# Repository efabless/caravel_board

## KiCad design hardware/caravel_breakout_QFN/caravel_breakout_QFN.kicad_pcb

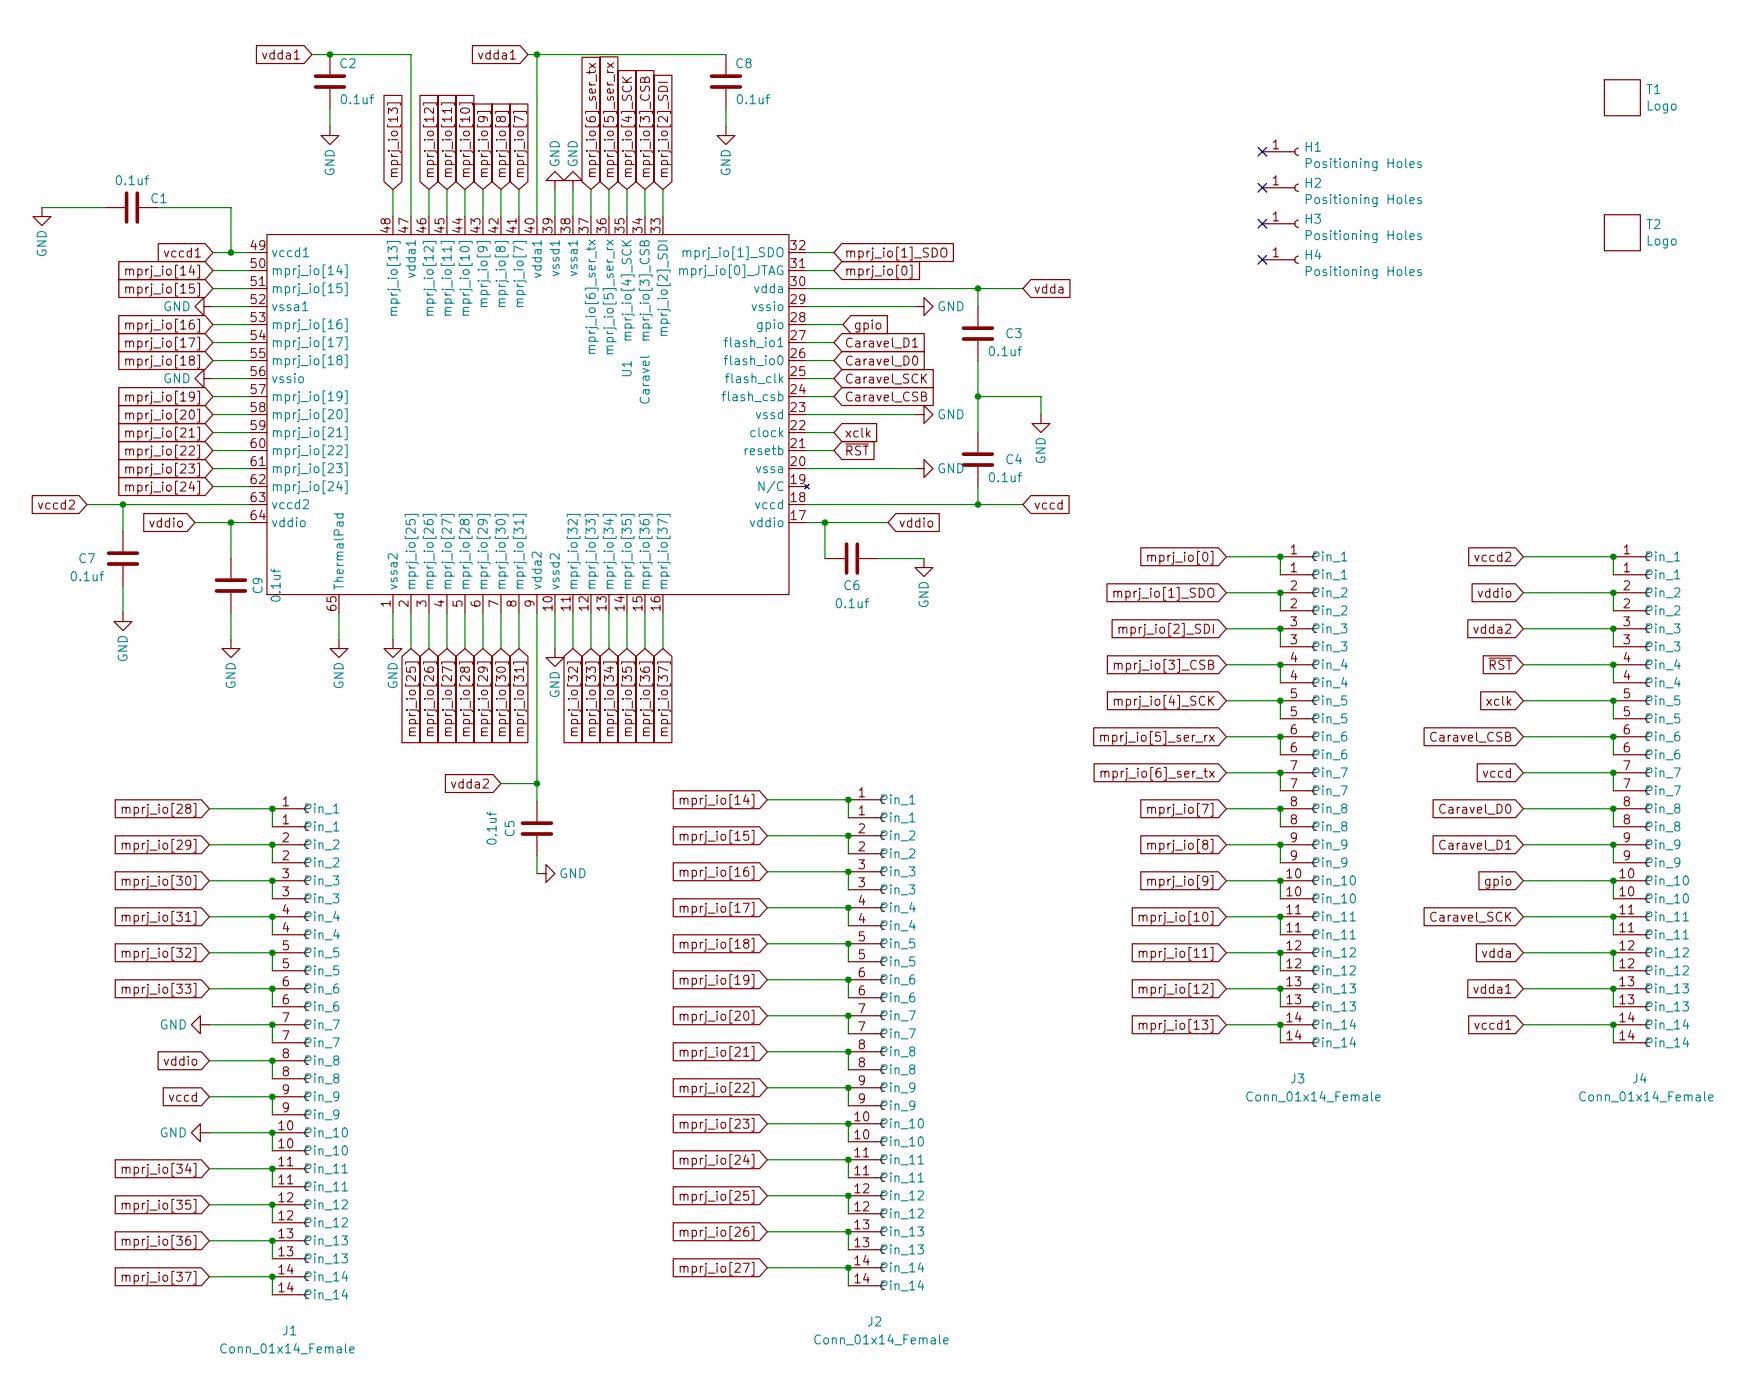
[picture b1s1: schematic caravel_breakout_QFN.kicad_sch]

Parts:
C1, C2, C3, C4, C5, C6, C7, C8, C9: 0.1uf; C_0402_1005Metric
H1, H2, H3, H4: Positioning Holes; MountingHole_2.2mm_M2_ISO7380_Pad
J1, J2, J3, J4: Conn_01x14_Female; Caravel_Breakout_Connectors_2x14
T1: Logo; logo_small
T2: Logo; ef_logo
U1: Caravel; QFN-64-1EP_9x9mm_P0.5mm_EP7.65x7.65mm

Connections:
Caravel_CSB: J4.6, U1.24 (flash_csb)
Caravel_D0: J4.8, U1.26 (flash_io0)
Caravel_D1: J4.9, U1.27 (flash_io1)
Caravel_SCK: J4.11, U1.25 (flash_clk)
GND: C1.1, C2.2, C3.2, C4.1, C5.1, C6.1, C7.1, C8.2, C9.1, J1.7, J1.10, U1.1 (vssa2), U1.10 (vssd2), U1.20 (vssa), U1.23 (vssd), U1.29 (vssio), U1.38 (vssa1), U1.39 (vssd1), U1.52 (vssa1), U1.56 (vssio), U1.65 (ThermalPad)
gpio: J4.10, U1.28 (gpio)
mprj_io[0]: J3.1, U1.31 (mprj_io[0]_JTAG)
mprj_io[1]_SDO: J3.2, U1.32 (mprj_io[1]_SDO)
mprj_io[2]_SDI: J3.3, U1.33 (mprj_io[2]_SDI)
mprj_io[3]_CSB: J3.4, U1.34 (mprj_io[3]_CSB)
mprj_io[4]_SCK: J3.5, U1.35 (mprj_io[4]_SCK)
mprj_io[5]_ser_rx: J3.6, U1.36 (mprj_io[5]_ser_rx)
mprj_io[6]_ser_tx: J3.7, U1.37 (mprj_io[6]_ser_tx)
mprj_io[7]: J3.8, U1.41 (mprj_io[7])
mprj_io[8]: J3.9, U1.42 (mprj_io[8])
mprj_io[9]: J3.10, U1.43 (mprj_io[9])
mprj_io[10]: J3.11, U1.44 (mprj_io[10])
mprj_io[11]: J3.12, U1.45 (mprj_io[11])
mprj_io[12]: J3.13, U1.46 (mprj_io[12])
mprj_io[13]: J3.14, U1.48 (mprj_io[13])
mprj_io[14]: J2.1, U1.50 (mprj_io[14])
mprj_io[15]: J2.2, U1.51 (mprj_io[15])
mprj_io[16]: J2.3, U1.53 (mprj_io[16])
mprj_io[17]: J2.4, U1.54 (mprj_io[17])
mprj_io[18]: J2.5, U1.55 (mprj_io[18])
mprj_io[19]: J2.6, U1.57 (mprj_io[19])
mprj_io[20]: J2.7, U1.58 (mprj_io[20])
mprj_io[21]: J2.8, U1.59 (mprj_io[21])
mprj_io[22]: J2.9, U1.60 (mprj_io[22])
mprj_io[23]: J2.10, U1.61 (mprj_io[23])
mprj_io[24]: J2.11, U1.62 (mprj_io[24])
mprj_io[25]: J2.12, U1.2 (mprj_io[25])
mprj_io[26]: J2.13, U1.3 (mprj_io[26])
mprj_io[27]: J2.14, U1.4 (mprj_io[27])
mprj_io[28]: J1.1, U1.5 (mprj_io[28])
mprj_io[29]: J1.2, U1.6 (mprj_io[29])
mprj_io[30]: J1.3, U1.7 (mprj_io[30])
mprj_io[31]: J1.4, U1.8 (mprj_io[31])
mprj_io[32]: J1.5, U1.11 (mprj_io[32])
mprj_io[33]: J1.6, U1.12 (mprj_io[33])
mprj_io[34]: J1.11, U1.13 (mprj_io[34])
mprj_io[35]: J1.12, U1.14 (mprj_io[35])
mprj_io[36]: J1.13, U1.15 (mprj_io[36])
mprj_io[37]: J1.14, U1.16 (mprj_io[37])
vccd: C4.2, J1.9, J4.7, U1.18 (vccd)
vccd1: C1.2, J4.14, U1.49 (vccd1)
vccd2: C7.2, J4.1, U1.63 (vccd2)
vdda: C3.1, J4.12, U1.30 (vdda)
vdda1: C2.1, C8.1, J4.13, U1.40 (vdda1), U1.47 (vdda1)
vdda2: C5.2, J4.3, U1.9 (vdda2)
vddio: C6.2, C9.2, J1.8, J4.2, U1.17 (vddio), U1.64 (vddio)
xclk: J4.5, U1.22 (clock)
~RST: J4.4, U1.21 (resetb)

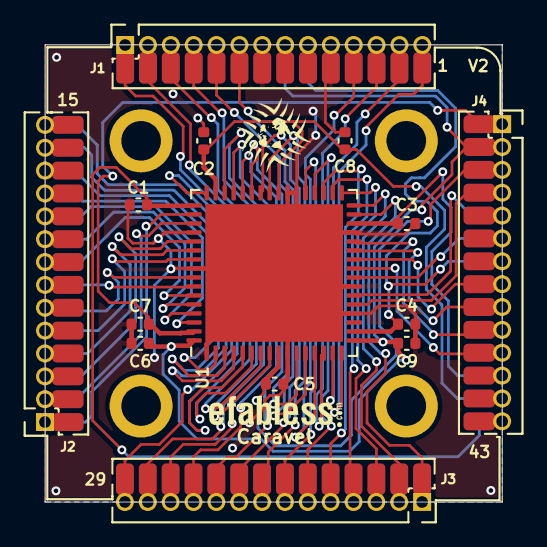
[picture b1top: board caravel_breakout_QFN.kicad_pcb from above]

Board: 2 copper layers, 25.4 x 25.4 mm, 20 parts (0 on the bottom side), 53 nets.

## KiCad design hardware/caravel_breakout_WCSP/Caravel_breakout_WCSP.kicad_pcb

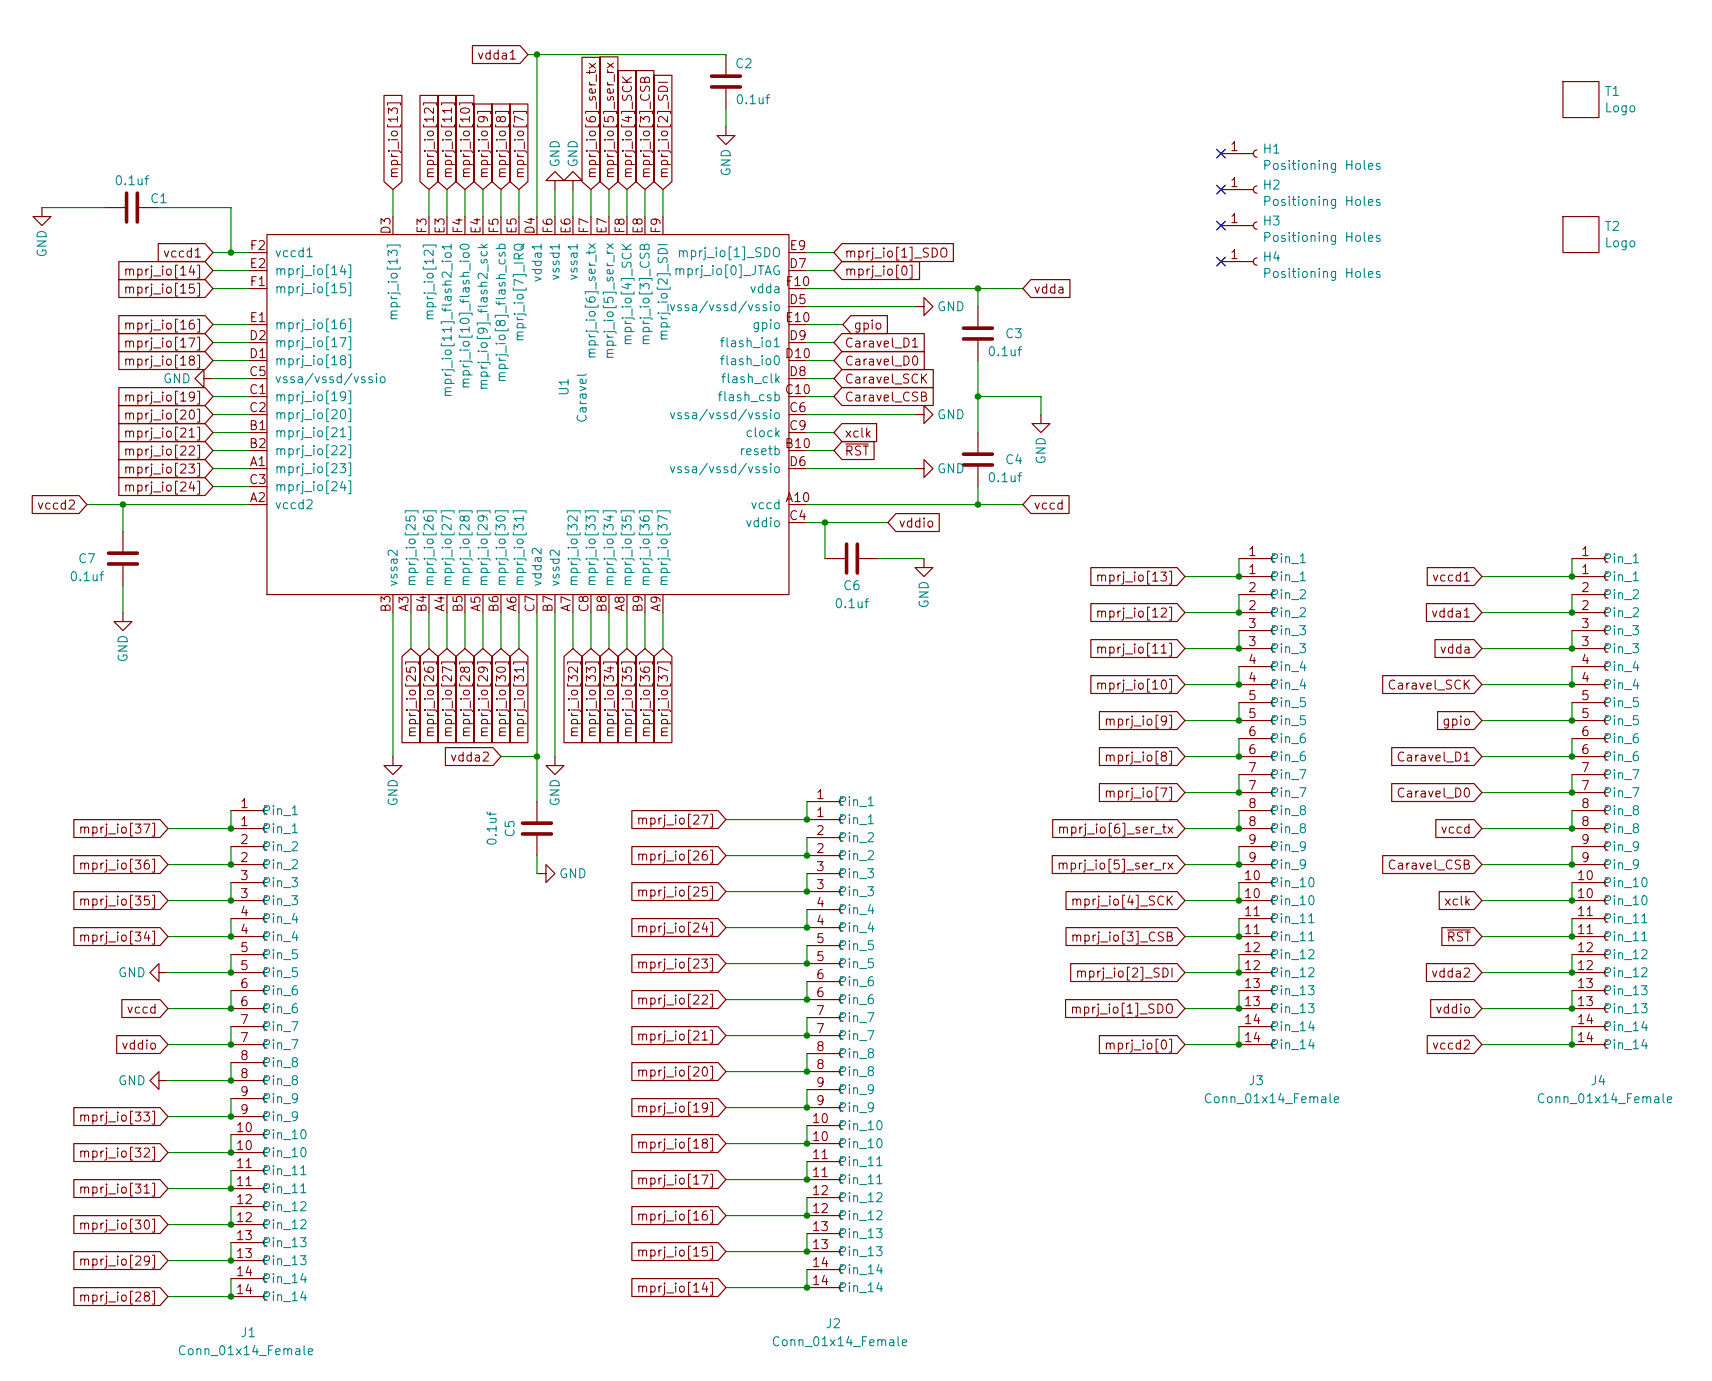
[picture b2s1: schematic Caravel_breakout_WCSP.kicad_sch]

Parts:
C1, C2, C3, C4, C5, C6, C7: 0.1uf; C_0603_1608Metric
H1, H2, H3, H4: Positioning Holes; MountingHole_2.2mm_M2_ISO7380_Pad
J1, J2, J3, J4: Conn_01x14_Female; Caravel_Breakout_Connectors_2x14
T1: Logo; logo
T2: Logo; ef_logo
U1: Caravel; Caravel_WCSP

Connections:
Caravel_CSB: J4.9, U1.C10 (flash_csb)
Caravel_D0: J4.7, U1.D10 (flash_io0)
Caravel_D1: J4.6, U1.D9 (flash_io1)
Caravel_SCK: J4.4, U1.D8 (flash_clk)
GND: C1.1, C2.2, C3.2, C4.1, C5.1, C6.1, C7.1, J1.5, J1.8, U1.B3 (vssa2), U1.B7 (vssd2), U1.C5 (vssa/vssd/vssio), U1.C6 (vssa/vssd/vssio), U1.D5 (vssa/vssd/vssio), U1.D6 (vssa/vssd/vssio), U1.E6 (vssa1), U1.F6 (vssd1)
gpio: J4.5, U1.E10 (gpio)
mprj_io[0]: J3.14, U1.D7 (mprj_io[0]_JTAG)
mprj_io[1]_SDO: J3.13, U1.E9 (mprj_io[1]_SDO)
mprj_io[2]_SDI: J3.12, U1.F9 (mprj_io[2]_SDI)
mprj_io[3]_CSB: J3.11, U1.E8 (mprj_io[3]_CSB)
mprj_io[4]_SCK: J3.10, U1.F8 (mprj_io[4]_SCK)
mprj_io[5]_ser_rx: J3.9, U1.E7 (mprj_io[5]_ser_rx)
mprj_io[6]_ser_tx: J3.8, U1.F7 (mprj_io[6]_ser_tx)
mprj_io[7]: J3.7, U1.E5 (mprj_io[7]_IRQ)
mprj_io[8]: J3.6, U1.F5 (mprj_io[8]_flash_csb)
mprj_io[9]: J3.5, U1.E4 (mprj_io[9]_flash2_sck)
mprj_io[10]: J3.4, U1.F4 (mprj_io[10]_flash_io0)
mprj_io[11]: J3.3, U1.E3 (mprj_io[11]_flash2_io1)
mprj_io[12]: J3.2, U1.F3 (mprj_io[12])
mprj_io[13]: J3.1, U1.D3 (mprj_io[13])
mprj_io[14]: J2.14, U1.E2 (mprj_io[14])
mprj_io[15]: J2.13, U1.F1 (mprj_io[15])
mprj_io[16]: J2.12, U1.E1 (mprj_io[16])
mprj_io[17]: J2.11, U1.D2 (mprj_io[17])
mprj_io[18]: J2.10, U1.D1 (mprj_io[18])
mprj_io[19]: J2.9, U1.C1 (mprj_io[19])
mprj_io[20]: J2.8, U1.C2 (mprj_io[20])
mprj_io[21]: J2.7, U1.B1 (mprj_io[21])
mprj_io[22]: J2.6, U1.B2 (mprj_io[22])
mprj_io[23]: J2.5, U1.A1 (mprj_io[23])
mprj_io[24]: J2.4, U1.C3 (mprj_io[24])
mprj_io[25]: J2.3, U1.A3 (mprj_io[25])
mprj_io[26]: J2.2, U1.B4 (mprj_io[26])
mprj_io[27]: J2.1, U1.A4 (mprj_io[27])
mprj_io[28]: J1.14, U1.B5 (mprj_io[28])
mprj_io[29]: J1.13, U1.A5 (mprj_io[29])
mprj_io[30]: J1.12, U1.B6 (mprj_io[30])
mprj_io[31]: J1.11, U1.A6 (mprj_io[31])
mprj_io[32]: J1.10, U1.A7 (mprj_io[32])
mprj_io[33]: J1.9, U1.C8 (mprj_io[33])
mprj_io[34]: J1.4, U1.B8 (mprj_io[34])
mprj_io[35]: J1.3, U1.A8 (mprj_io[35])
mprj_io[36]: J1.2, U1.B9 (mprj_io[36])
mprj_io[37]: J1.1, U1.A9 (mprj_io[37])
vccd: C4.2, J1.6, J4.8, U1.A10 (vccd)
vccd1: C1.2, J4.1, U1.F2 (vccd1)
vccd2: C7.2, J4.14, U1.A2 (vccd2)
vdda: C3.1, J4.3, U1.F10 (vdda)
vdda1: C2.1, J4.2, U1.D4 (vdda1)
vdda2: C5.2, J4.12, U1.C7 (vdda2)
vddio: C6.2, J1.7, J4.13, U1.C4 (vddio)
xclk: J4.10, U1.C9 (clock)
~RST: J4.11, U1.B10 (resetb)

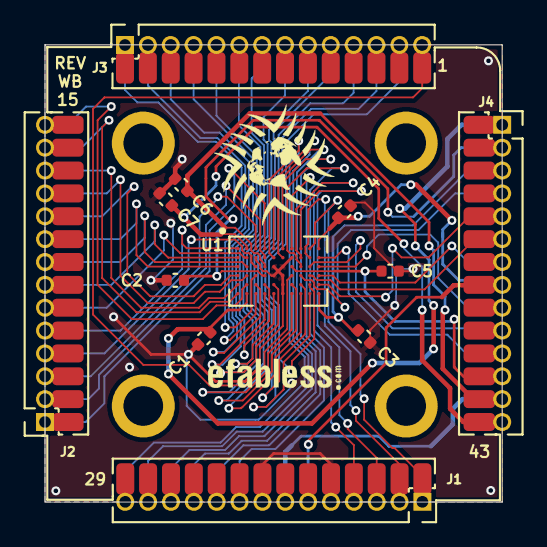
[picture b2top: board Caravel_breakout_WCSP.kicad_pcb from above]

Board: 2 copper layers, 25.4 x 25.4 mm, 18 parts (0 on the bottom side), 53 nets.

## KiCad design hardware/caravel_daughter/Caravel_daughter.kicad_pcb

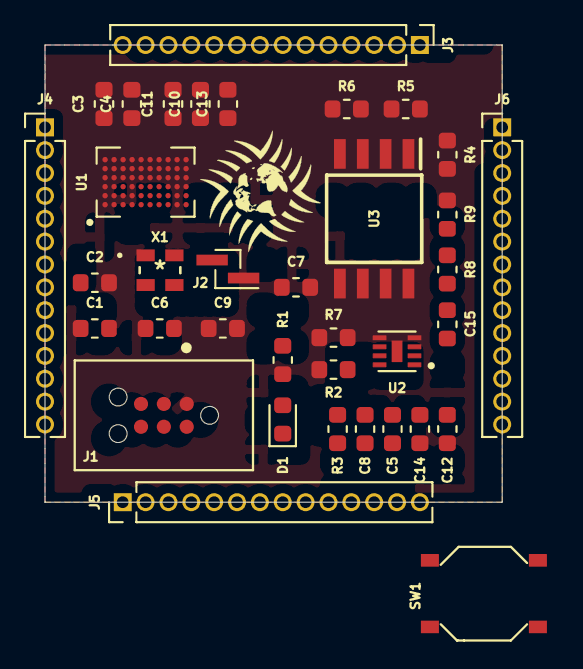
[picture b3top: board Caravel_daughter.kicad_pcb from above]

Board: 2 copper layers, 25.4 x 25.4 mm, 37 parts (0 on the bottom side), 57 nets, no tracks yet.

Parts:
C1, C2, C3, C4, C6, C7, C8, C9, C10, C11, C13, C15: 0.1uf; C_0603_1608Metric
C5: 10uf; C_0603_1608Metric
C12, C14: 2.2uf; C_0603_1608Metric
D1: LED - 17-215SURC/S530-A2/TR8; LED_0603_1608Metric
J1: TC2030-IDC-NL; TAG_TC2030-IDC-NL
J2: Conn_01x02_Male; PinHeader_1x02_P1.00mm_Vertical_SMD_Pin1Left
J3, J4, J5, J6: Conn_01x14_Female; PinHeader_1x14_P1.27mm_Vertical
R1: 82 - 0805W8F820JT5E; R_0603_1608Metric
R2, R3: 100; R_0603_1608Metric
R4, R5, R6, R7, R8, R9: 10k; R_0603_1608Metric
SW1: SW_Push - SKQGADE010; SW4-SMD-5.2X5.2X1.5MM
T1: Logo; logo
U1: Caravel; Caravel_WCSP
U2: MIC5350-SGYMT-TR; SON50P200X200X60-9N
U3: W25Q32FVSS; SOIC127P790X216-8N
X1: DSC6001_10MHZ; DSC6001JE1A-010.0000

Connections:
+1V8: C11.2, C14.2, J6.2, J6.3, U1.A10, U2.7
+3V3: C12.2, C13.1, J6.6, J6.7, R1.1, U1.F10, U2.8
+5V: C5.2, J1.6, J6.14, R2.2, R3.2, U2.1
Caravel_CSB: R4.1, U1.C10, U3.1
Caravel_D0: R7.1, U1.D10, U3.5
Caravel_D1: R5.1, U1.D9, U3.2
Caravel_SCK: R8.1, U1.D8, U3.6
GND: C1.1, C2.1, C3.2, C4.1, C5.1, C6.1, C7.2, C8.1, C9.1, C10.1, C11.1, C12.1, C13.2, C14.1, C15.2, J1.1, J2.2, SW1.2, U1.B3, U1.B7, U1.C5, U1.C6, U1.D5, U1.D6, U1.E6, U1.F6, U2.2, U2.9, U3.4, X1.2
unnamed: C8.2, U2.3
unnamed: D1.2, R1.2
unnamed: J2.1, X1.1
unnamed: R2.1, U2.4
unnamed: R3.1, U2.5
unnamed: R6.1, U3.3
unnamed: R9.1, U3.7
gpio: D1.1, U1.E10
mprj_io[0]: J3.1, U1.D7
mprj_io[1]_SDO: J3.2, U1.E9
mprj_io[2]_SDI: J3.3, U1.F9
mprj_io[3]_CSB: J3.4, U1.E8
mprj_io[4]_SCK: J3.5, U1.F8
mprj_io[5]_ser_rx: J1.2, J3.6, U1.E7
mprj_io[6]_ser_tx: J1.3, J3.7, U1.F7
mprj_io[7]: J3.8, U1.E5
mprj_io[8]: J3.9, U1.F5
mprj_io[9]: J3.10, U1.E4
mprj_io[10]: J3.11, U1.F4
mprj_io[11]: J3.12, U1.E3
mprj_io[12]: J3.13, U1.F3
mprj_io[13]: J3.14, U1.D3
mprj_io[14]: J4.1, U1.E2
mprj_io[15]: J4.2, U1.F1
mprj_io[16]: J4.3, U1.E1
mprj_io[17]: J4.4, U1.D2
mprj_io[18]: J4.5, U1.D1
mprj_io[19]: J4.6, U1.C1
mprj_io[20]: J4.7, U1.C2
mprj_io[21]: J4.8, U1.B1
mprj_io[22]: J4.9, U1.B2
mprj_io[23]: J4.10, U1.A1
mprj_io[24]: J4.11, U1.C3
mprj_io[25]: J4.12, U1.A3
mprj_io[26]: J4.13, U1.B4
mprj_io[27]: J4.14, U1.A4
mprj_io[28]: J5.1, U1.B5
mprj_io[29]: J5.2, U1.A5
mprj_io[30]: J5.3, U1.B6
mprj_io[31]: J5.4, U1.A6
mprj_io[32]: J5.5, U1.A7
mprj_io[33]: J5.6, U1.C8
vccd1: C3.1, J6.4, U1.F2
vccd2: C1.2, J6.1, U1.A2
vdda1: C4.2, C7.1, J6.8, U1.D4
vdda2: C6.2, J6.5, U1.C7
vddio: C2.2, C9.2, C10.2, C15.1, R4.2, R5.2, R6.2, R7.2, R8.2, R9.2, U1.C4, U3.8, X1.4
xclk: U1.C9, X1.3
~RST: SW1.1, U1.B10

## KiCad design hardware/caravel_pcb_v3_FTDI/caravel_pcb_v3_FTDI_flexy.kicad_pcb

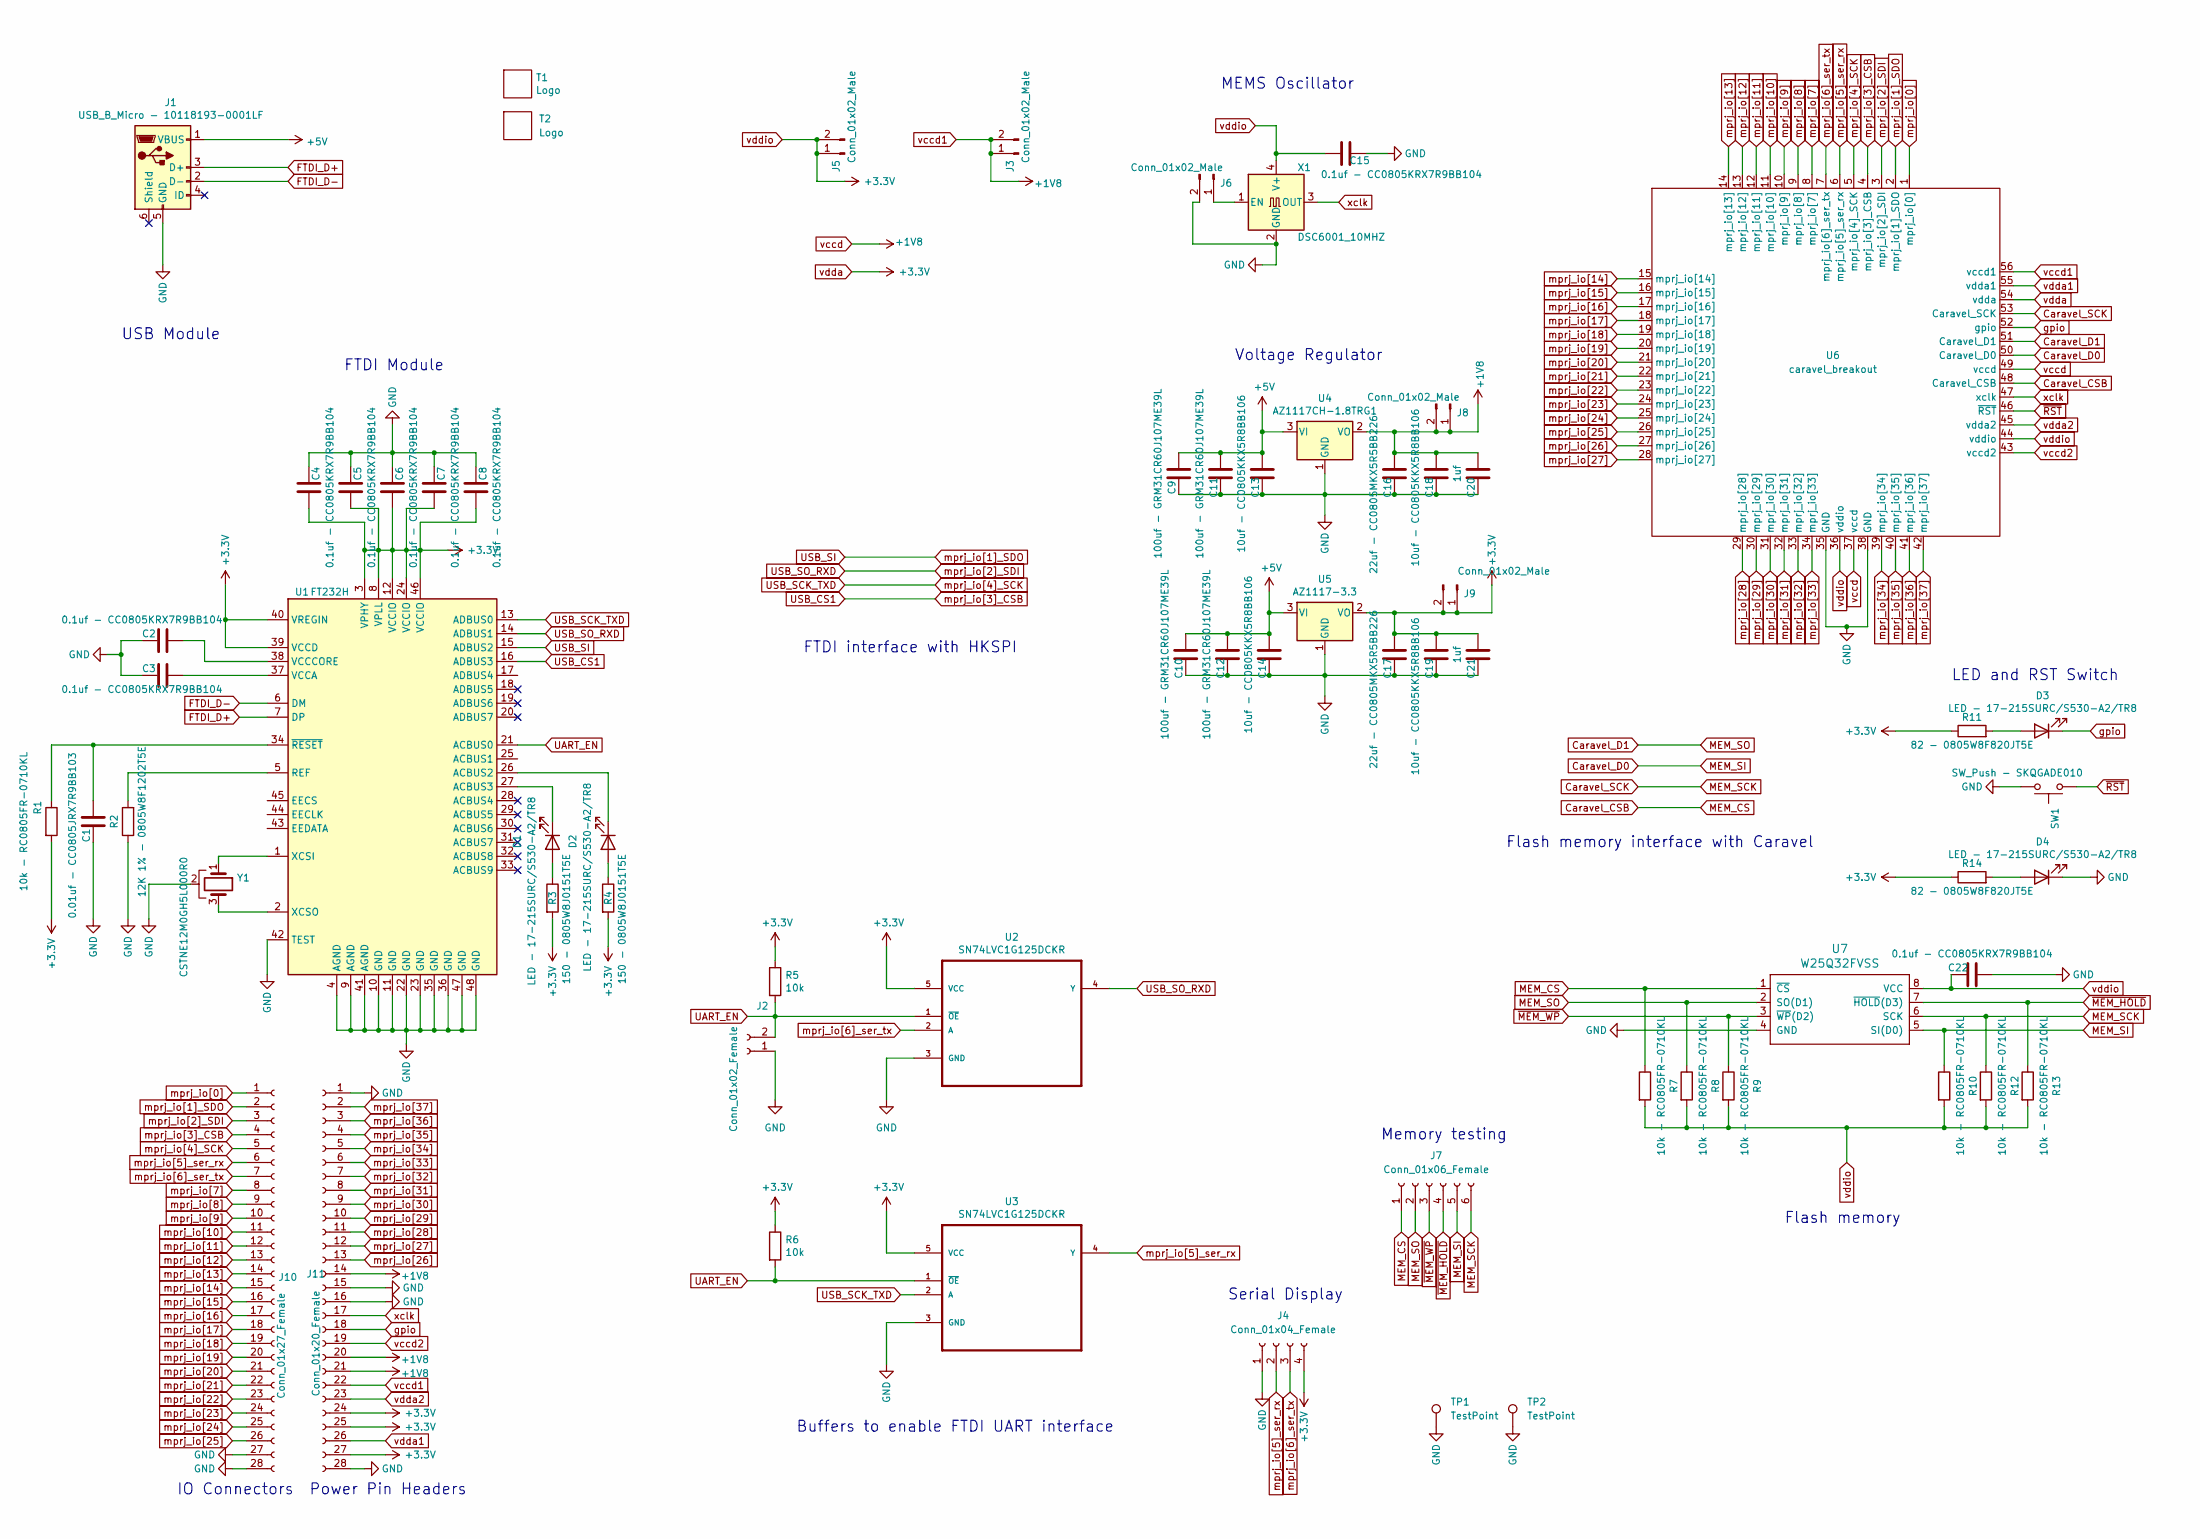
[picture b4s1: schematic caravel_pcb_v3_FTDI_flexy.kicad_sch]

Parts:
C1: 0.01uf - CC0805JRX7R9BB103; C_0805_2012Metric
C2, C3, C4, C5, C6, C7, C8, C15, C22: 0.1uf - CC0805KRX7R9BB104; C_0805_2012Metric
C9, C10, C11, C12: 100uf - GRM31CR60J107ME39L; C_1206_3216Metric
C13, C14, C18, C19: 10uf - CC0805KKX5R8BB106; C_0805_2012Metric
C16, C17: 22uf - CC0805MKX5R5BB226; C_0805_2012Metric
C20, C21: 1uf; C_0805_2012Metric
D1, D2, D3, D4: LED - 17-215SURC/S530-A2/TR8; LED_1206_3216Metric
J1: USB_B_Micro - 10118193-0001LF; FCI_10118193-0001LF
J2: Conn_01x02_Female; PinHeader_1x02_P2.54mm_Vertical
J3, J5, J6, J8, J9: Conn_01x02_Male; PinHeader_1x02_P2.54mm_Vertical
J4: Conn_01x04_Female; PinHeader_1x04_P2.54mm_Vertical
J7: Conn_01x06_Female; PinHeader_1x06_P2.54mm_Vertical
J10: Conn_01x27_Female; PinHeader_1x27_P2.54mm_Vertical
J11: Conn_01x20_Female; PinHeader_1x20_P2.54mm_Vertical
R1, R7, R8, R9, R10, R12, R13: 10k - RC0805FR-0710KL; R_0805_2012Metric
R2: 12K 1% - 0805W8F1202T5E; R_0805_2012Metric
R3, R4: 150 - 0805W8J0151T5E; R_0805_2012Metric
R5, R6: 10k; R_0805_2012Metric
R11, R14: 82 - 0805W8F820JT5E; R_0805_2012Metric
SW1: SW_Push - SKQGADE010; SW4-SMD-5.2X5.2X1.5MM
T1: Logo; logo
T2: Logo; ef_logo
TP1, TP2: TestPoint; TestPoint_Bridge_Pitch2.54mm_Drill1.0mm
U1: FT232H; QFN-48-1EP_8x8mm_P0.5mm_EP6.2x6.2mm
U2, U3: SN74LVC1G125DCKR; SOT65P210X110-5N
U4: AZ1117CH-1.8TRG1; SOT-223
U5: AZ1117-3.3; SOT-223
U6: caravel_breakout; caravel_breakout_flexy
U7: W25Q32FVSS; SOIC127P790X216-8N
X1: DSC6001_10MHZ; DSC6001JE1A-010.0000
Y1: CSTNE12M0GH5L000R0

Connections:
+5V: C9.2, C10.2, C11.2, C12.2, C13.2, C14.2, J1.1 (VBUS), U4.3 (VI), U5.3 (VI)
Caravel_CSB: J7.1, R7.1, U6.48 (Caravel_CSB), U7.1 (~CS)
Caravel_D0: J7.5, R10.1, U6.50 (Caravel_D0), U7.5 (SI(D0))
Caravel_D1: J7.2, R8.1, U6.51 (Caravel_D1), U7.2 (SO(D1))
Caravel_SCK: J7.6, R12.1, U6.53 (Caravel_SCK), U7.6 (SCK)
FTDI_D+: J1.3 (D+), U1.7 (DP)
FTDI_D-: J1.2 (D-), U1.6 (DM)
GND: C1.1, C2.1, C3.1, C4.1, C5.1, C6.1, C7.1, C8.1, C9.1, C10.1, C11.1, C12.1, C13.1, C14.1, C15.1, C16.1, C17.1, C18.1, C19.1, C20.1, C21.1, C22.2, D4.1 (K), J1.5 (GND), J2.1, J4.1, J6.2, J10.27, J10.28, J11.1, J11.15, J11.16, J11.28, R2.1, SW1.2, TP1.1, TP2.1, U1.4 (AGND), U1.9 (AGND), U1.10 (GND), U1.11 (GND), U1.22 (GND), U1.23 (GND), U1.35 (GND), U1.36 (GND), U1.41 (AGND), U1.42 (TEST), U1.47 (GND), U1.48 (GND), U2.3 (GND), U3.3 (GND), U4.1 (GND), U5.1 (GND), U6.35 (GND), U6.38 (GND), U7.4 (GND), X1.2 (GND), Y1.2
unnamed: C1.2, R1.1, U1.34 (~RESET)
unnamed: C2.2, U1.38 (VCCCORE)
unnamed: C3.2, U1.37 (VCCA)
unnamed: D1.1 (K), U1.27 (ACBUS3)
unnamed: D1.2 (A), R3.1
unnamed: D2.1 (K), U1.26 (ACBUS2)
unnamed: D2.2 (A), R4.1
unnamed: D3.2 (A), R11.2
unnamed: D4.2 (A), R14.2
unnamed: J6.1, X1.1 (EN)
unnamed: R2.2, U1.5 (REF)
unnamed: U1.1 (XCSI), Y1.1
unnamed: U1.2 (XCSO), Y1.3
UART_EN: J2.2, R5.2, R6.2, U1.21 (ACBUS0), U2.1 (~OE), U3.1 (~OE)
USB_CS1: J10.4, U1.16 (ADBUS3), U6.4 (mprj_io[3]_CSB)
USB_SCK_TXD: J10.5, U1.13 (ADBUS0), U3.2 (A), U6.5 (mprj_io[4]_SCK)
USB_SI: J10.2, U1.15 (ADBUS2), U6.2 (mprj_io[1]_SDO)
USB_SO_RXD: J10.3, U1.14 (ADBUS1), U2.4 (Y), U6.3 (mprj_io[2]_SDI)
gpio: D3.1 (K), J11.18, U6.52 (gpio)
mprj_io[0]: J10.1, U6.1 (mprj_io[0])
mprj_io[5]_ser_rx: J4.2, J10.6, U3.4 (Y), U6.6 (mprj_io[5]_ser_rx)
mprj_io[6]_ser_tx: J4.3, J10.7, U2.2 (A), U6.7 (mprj_io[6]_ser_tx)
mprj_io[7]: J10.8, U6.8 (mprj_io[7])
mprj_io[8]: J10.9, U6.9 (mprj_io[8])
mprj_io[9]: J10.10, U6.10 (mprj_io[9])
mprj_io[10]: J10.11, U6.11 (mprj_io[10])
mprj_io[11]: J10.12, U6.12 (mprj_io[11])
mprj_io[12]: J10.13, U6.13 (mprj_io[12])
mprj_io[13]: J10.14, U6.14 (mprj_io[13])
mprj_io[14]: J10.15, U6.15 (mprj_io[14])
mprj_io[15]: J10.16, U6.16 (mprj_io[15])
mprj_io[16]: J10.17, U6.17 (mprj_io[16])
mprj_io[17]: J10.18, U6.18 (mprj_io[17])
mprj_io[18]: J10.19, U6.19 (mprj_io[18])
mprj_io[19]: J10.20, U6.20 (mprj_io[19])
mprj_io[20]: J10.21, U6.21 (mprj_io[20])
mprj_io[21]: J10.22, U6.22 (mprj_io[21])
mprj_io[22]: J10.23, U6.23 (mprj_io[22])
mprj_io[23]: J10.24, U6.24 (mprj_io[23])
mprj_io[24]: J10.25, U6.25 (mprj_io[24])
mprj_io[25]: J10.26, U6.26 (mprj_io[25])
mprj_io[26]: J11.13, U6.27 (mprj_io[26])
mprj_io[27]: J11.12, U6.28 (mprj_io[27])
mprj_io[28]: J11.11, U6.29 (mprj_io[28])
mprj_io[29]: J11.10, U6.30 (mprj_io[29])
mprj_io[30]: J11.9, U6.31 (mprj_io[30])
mprj_io[31]: J11.8, U6.32 (mprj_io[31])
mprj_io[32]: J11.7, U6.33 (mprj_io[32])
mprj_io[33]: J11.6, U6.34 (mprj_io[33])
mprj_io[34]: J11.5, U6.39 (mprj_io[34])
mprj_io[35]: J11.4, U6.40 (mprj_io[35])
mprj_io[36]: J11.3, U6.41 (mprj_io[36])
mprj_io[37]: J11.2, U6.42 (mprj_io[37])
vccd1: C16.2, C18.2, C20.2, J3.1, J3.2, J8.1, J8.2, J11.14, J11.20, J11.21, J11.22, U4.2 (VO), U6.37 (vccd), U6.49 (vccd), U6.56 (vccd1)
vccd2: J11.19, U6.43 (vccd2)
vdda: C4.2, C5.2, C6.2, C7.2, C8.2, C15.2, C17.2, C19.2, C21.2, C22.1, J4.4, J5.1, J5.2, J9.1, J9.2, J11.24, J11.25, J11.27, R1.2, R3.2, R4.2, R5.1, R6.1, R7.2, R8.2, R9.2, R10.2, R11.1, R12.2, R13.2, R14.1, U1.3 (VPHY), U1.8 (VPLL), U1.12 (VCCIO), U1.24 (VCCIO), U1.39 (VCCD), U1.40 (VREGIN), U1.46 (VCCIO), U2.5 (VCC), U3.5 (VCC), U5.2 (VO), U6.36 (vddio), U6.44 (vddio), U6.54 (vdda), U7.8 (VCC), X1.4 (V+)
vdda1: J11.26, U6.55 (vdda1)
vdda2: J11.23, U6.45 (vdda2)
xclk: J11.17, U6.47 (xclk), X1.3 (OUT)
~MEM_HOLD: J7.4, R13.1, U7.7 (~HOLD(D3))
~MEM_WP: J7.3, R9.1, U7.3 (~WP(D2))
~RST: SW1.1, U6.46 (~RST)

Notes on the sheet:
Serial Display
LED and RST Switch
Flash memory interface with Caravel
Flash memory
Memory testing
FTDI interface with HKSPI
Power Pin Headers
Voltage Regulator
IO Connectors
FTDI Module
USB Module
MEMS Oscillator
Buffers to enable FTDI UART interface

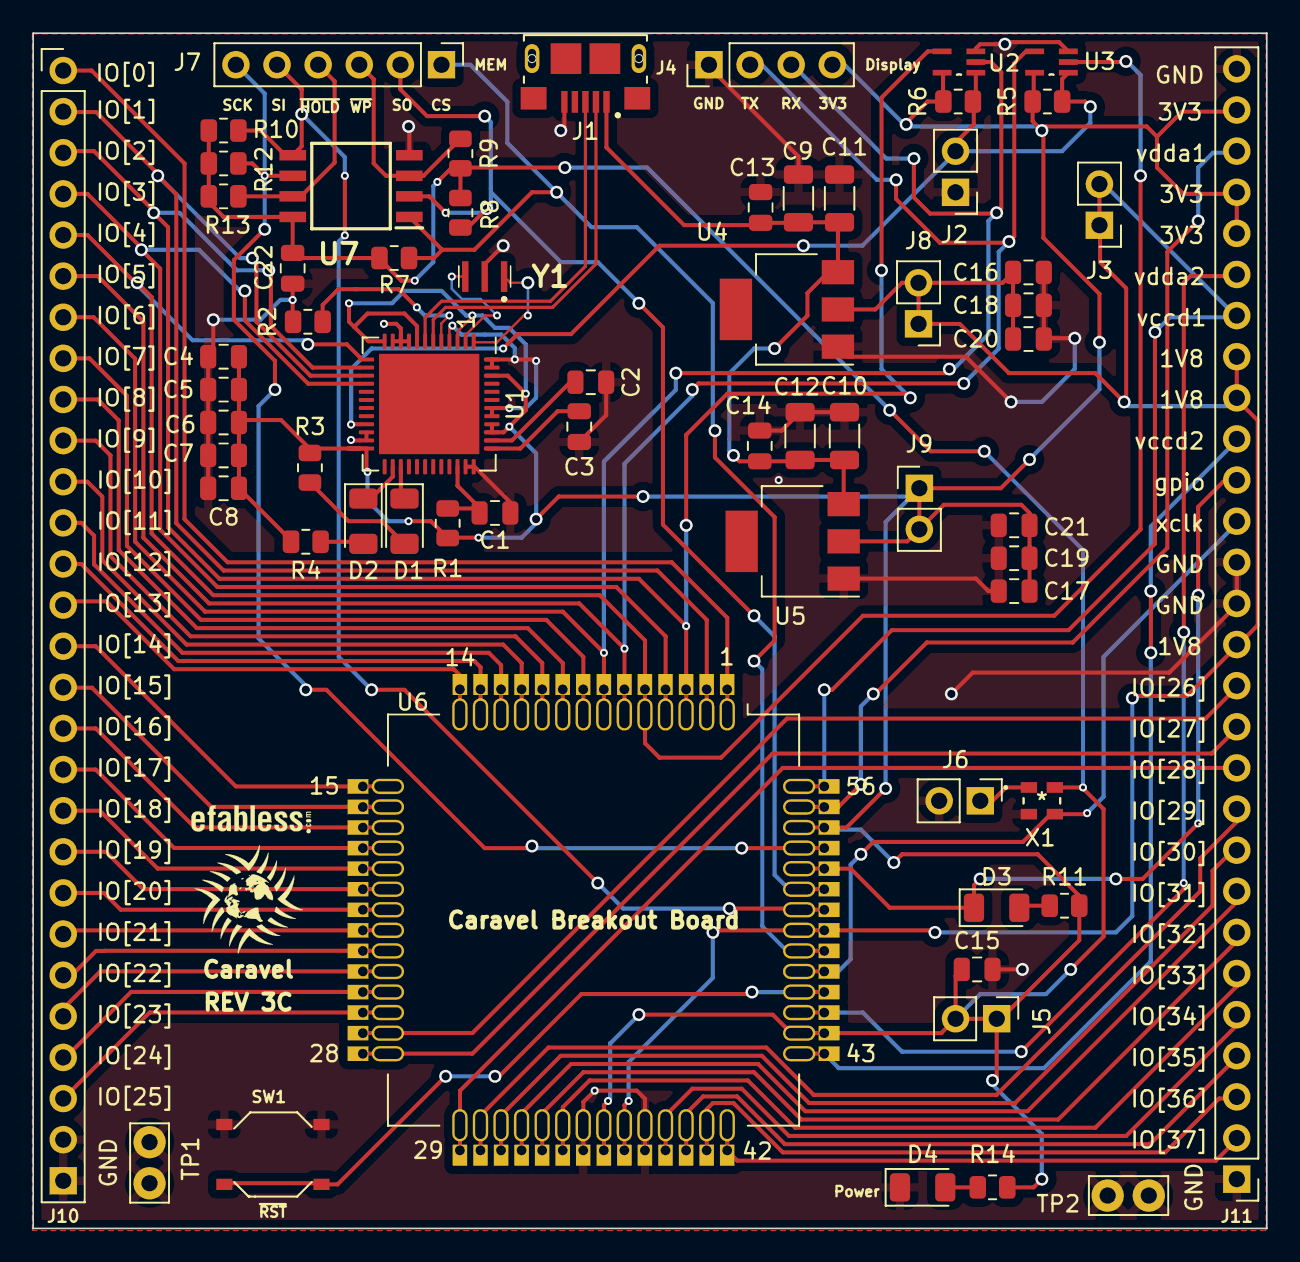
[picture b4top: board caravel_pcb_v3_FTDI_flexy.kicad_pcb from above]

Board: 2 copper layers, 76.2 x 73.8 mm, 65 parts (0 on the bottom side), 70 nets.

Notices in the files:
parts and their libraries:
Copyright 2016 Accelerated Designs. All rights reserved.
